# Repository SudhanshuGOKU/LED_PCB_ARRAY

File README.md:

# LED_PCB_ARRAY
Schematic and PCB Layout of LED_PCB_ARRAY ( 12 Volt ) ( White and Yellow )

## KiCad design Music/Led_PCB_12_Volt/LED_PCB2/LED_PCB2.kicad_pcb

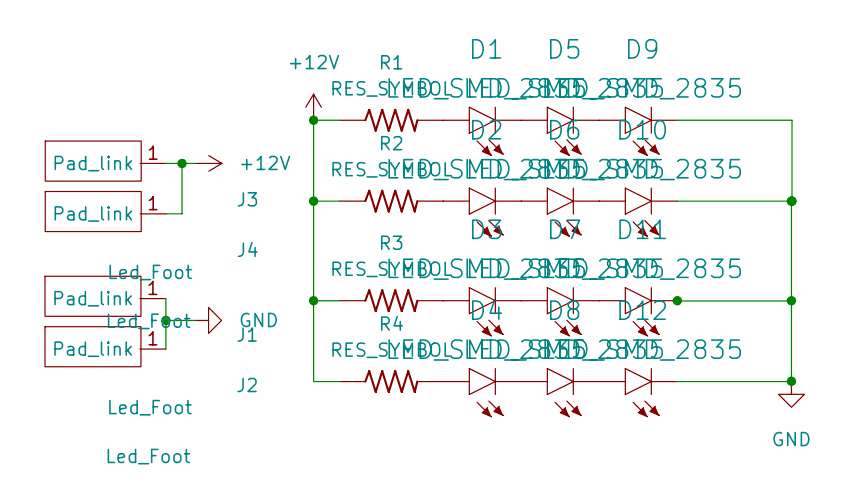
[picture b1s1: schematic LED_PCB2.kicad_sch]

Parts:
D1, D2, D3, D4, D5, D6, D7, D8, D9, D10, D11, D12: LED_SMD_2835; LED_PLCC_2835_Handsoldering
J1, J2, J3, J4: Led_Foot; Led_Footprint
R1, R2, R3, R4: RES_SYMBOL; R_0805_2012Metric; Tolerance .1%; Voltage_Rating 100 V

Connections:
+12V: J3.1 (Pad_link), J4.1 (Pad_link), R1.1, R2.1, R3.1, R4.1
GND: D9.1 (C), D10.1 (C), D11.1 (C), D12.1 (C), J1.1 (Pad_link), J2.1 (Pad_link)
unnamed: D1.1 (C), D5.2 (A)
unnamed: D1.2 (A), R1.2
unnamed: D2.1 (C), D6.2 (A)
unnamed: D2.2 (A), R2.2
unnamed: D3.1 (C), D7.2 (A)
unnamed: D3.2 (A), R3.2
unnamed: D4.1 (C), D8.2 (A)
unnamed: D4.2 (A), R4.2
unnamed: D5.1 (C), D9.2 (A)
unnamed: D6.1 (C), D10.2 (A)
unnamed: D7.1 (C), D11.2 (A)
unnamed: D8.1 (C), D12.2 (A)

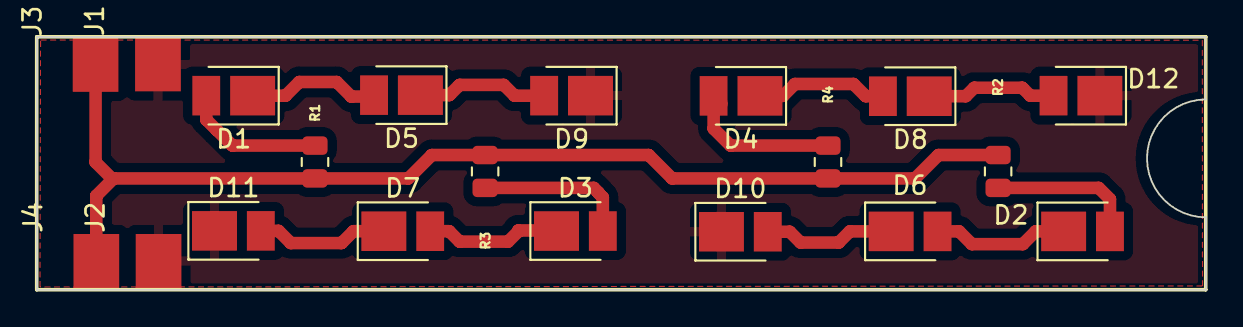
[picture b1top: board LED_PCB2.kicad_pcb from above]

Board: 2 copper layers, 65.0 x 14.0 mm, 20 parts (0 on the bottom side), 14 nets.

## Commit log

2023-04-25 hello word
